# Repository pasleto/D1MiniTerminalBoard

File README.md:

Wemos D1 Mini Terminal Board
============================
© 2019 - Tomáš Pásler - github.com/pasleto

INFO
----
PCB design is saved as an EAGLE project. Edit layers visibility for top/bottom view.

LICENSE
-------
Licensed under the TAPR Open Hardware License (www.tapr.org/OHL).

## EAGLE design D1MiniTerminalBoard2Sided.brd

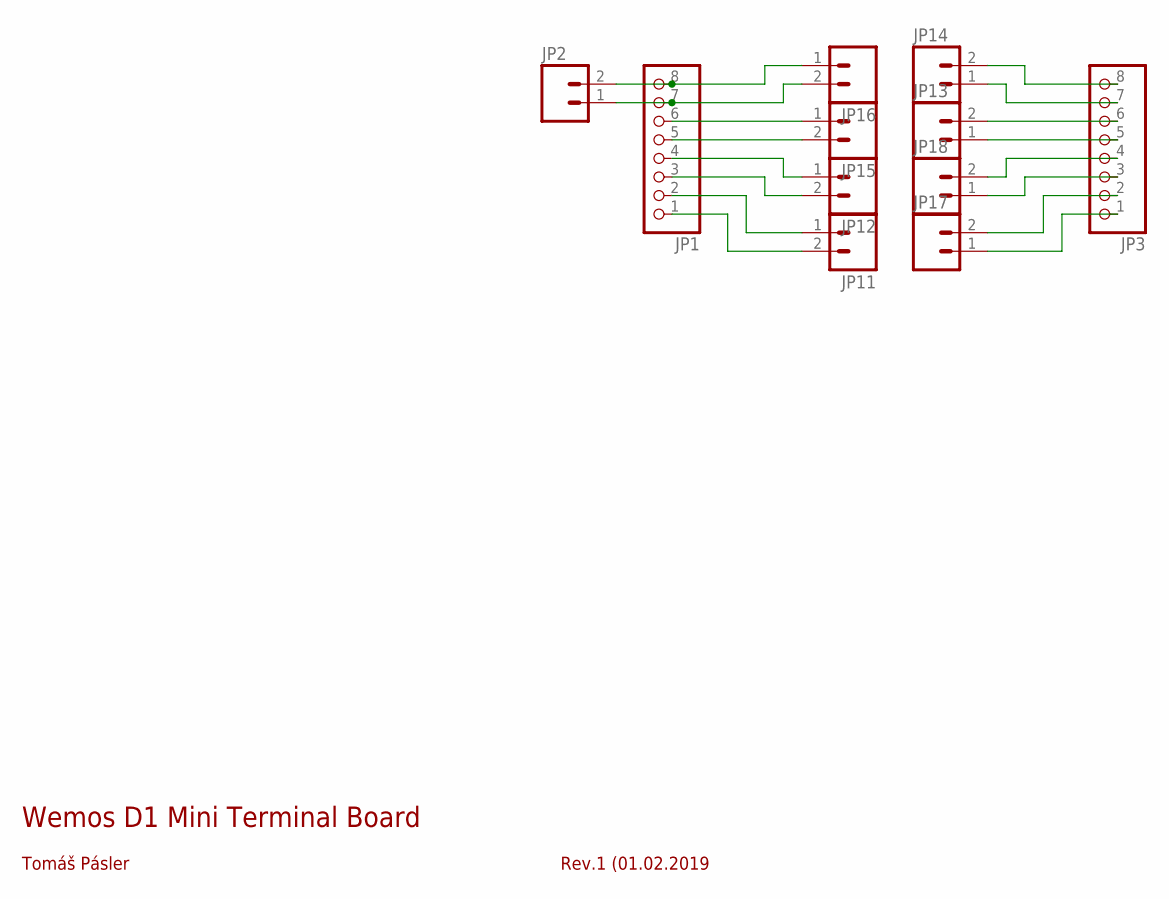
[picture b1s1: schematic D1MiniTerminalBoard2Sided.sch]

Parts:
JP1, JP3: PINHD-1X8; 1X08
JP2, JP11, JP12, JP13, JP14, JP15, JP16, JP17, JP18: M023.5MM; SCREWTERMINAL-3.5MM-2

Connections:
unnamed: JP1.8, JP2.2, JP16.1
unnamed: JP1.7, JP2.1, JP16.2
unnamed: JP1.1, JP11.2
unnamed: JP1.2, JP11.1
unnamed: JP1.3, JP12.2
unnamed: JP1.4, JP12.1
unnamed: JP1.5, JP15.2
unnamed: JP1.6, JP15.1
unnamed: JP3.4, JP18.2
unnamed: JP3.3, JP18.1
unnamed: JP3.8, JP14.2
unnamed: JP3.7, JP14.1
unnamed: JP3.6, JP13.2
unnamed: JP3.5, JP13.1
unnamed: JP3.2, JP17.2
unnamed: JP3.1, JP17.1

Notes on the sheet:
Tomáš Pásler
Wemos D1 Mini Terminal Board
Rev.1 (01.02.2019

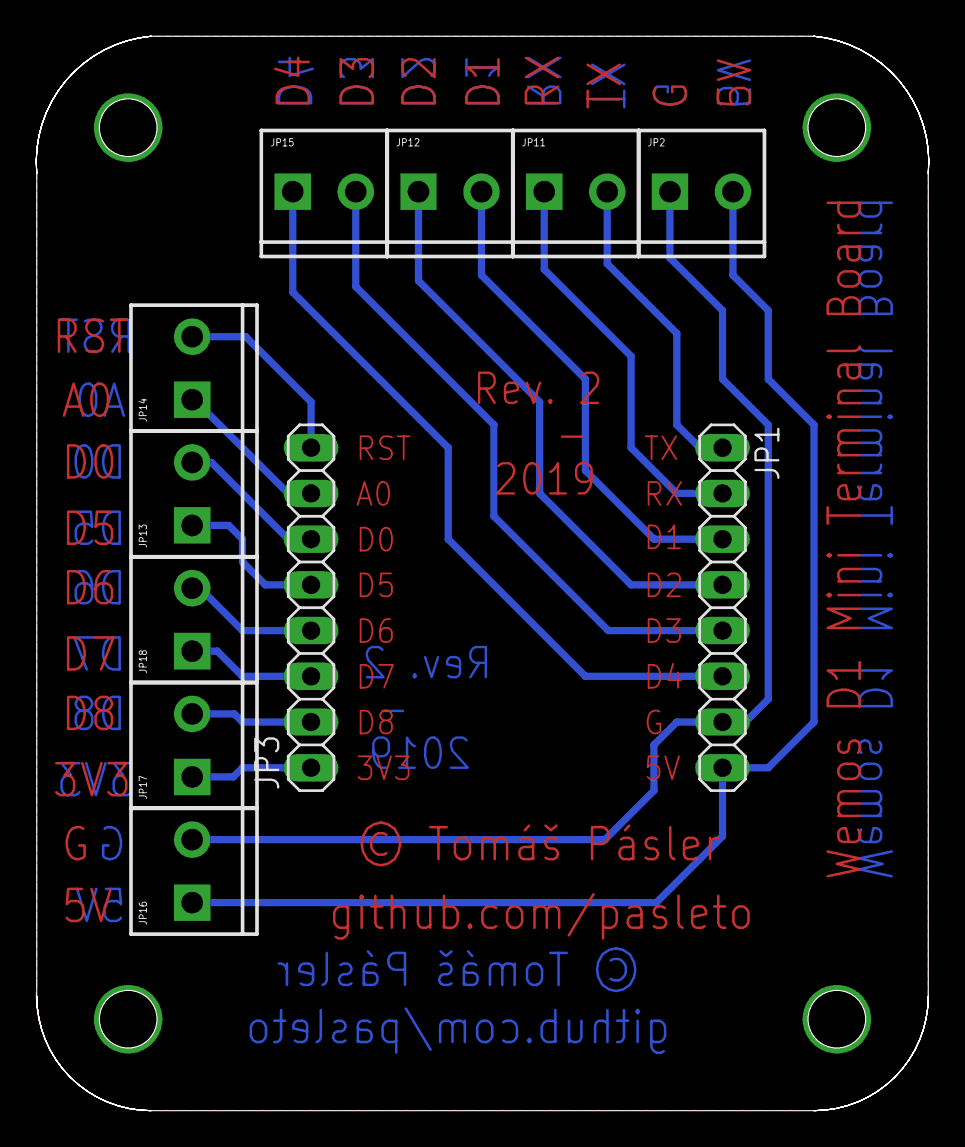
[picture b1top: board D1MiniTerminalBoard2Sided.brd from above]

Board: 2 copper layers, 49.6 x 59.7 mm, 11 parts (0 on the bottom side), 16 nets.

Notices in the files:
D1MiniTerminalBoard2Sided.brd:
© Tomáš Pásler
